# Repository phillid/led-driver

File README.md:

# LM3409HV LED Driver Boards

These are Kicad files for a 450 mA constant current LED driver built around
the LM3409HV, based mostly on the sample schematic in the TI datasheet.

It is designed for 48 volts in and 450 mA CC out, to drive Cree's 16.7 watt
LEDs with Vf of 37 volts.

The PCB measures about 34x32 mm.

More concrete and interesting details to follow as I send the boards to
manufacture, build them up, find the glaring errors I'm too blind to see,
and let the magic smoke out of some components 😜

## Version history

* **v1.1** (BOM change)
	This version changes R2 so that the UVLO is programmed for 43 V turn-on.
	This is to avoid over-driving the LEDs when the power supply voltage is
	low enough to make the driver incapable of reaching the peak LED current,
	which otherwise results in a raising of the average current.
* **v1**
	First, and prototype, revision. Started design in 2017 and finally got
	around to getting boards manufactured in May 2019 after taking a long
	break from the project. These are the first boards to be manufactured.

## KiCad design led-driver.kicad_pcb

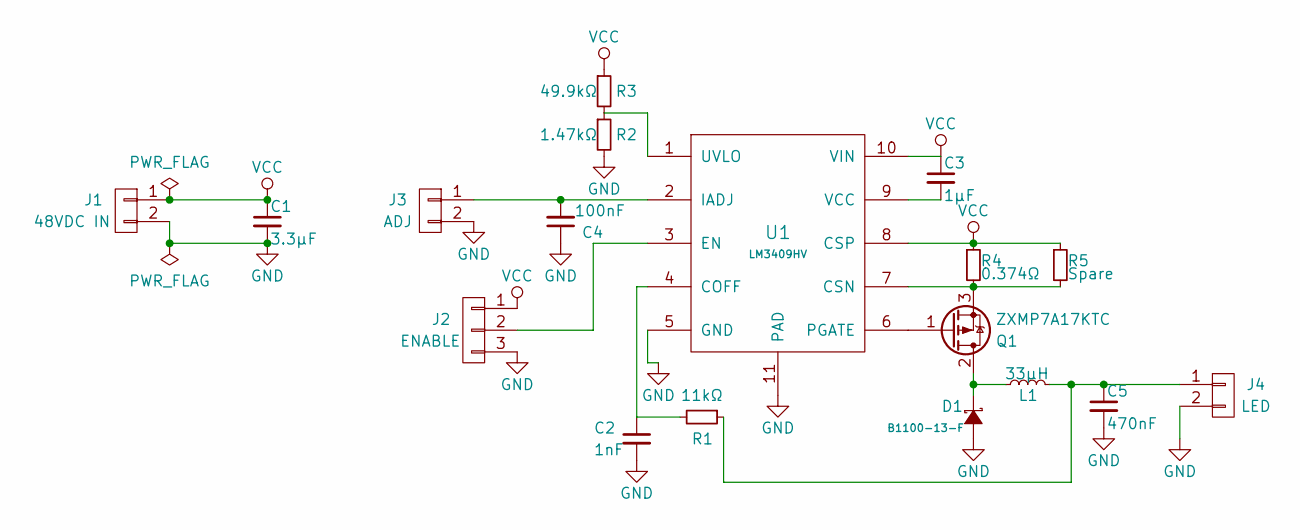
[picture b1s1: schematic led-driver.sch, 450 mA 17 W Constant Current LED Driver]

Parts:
C1: 3.3µF; CP_Elec_5x5.3
C2: 1nF; C_0805
C3: 1µF; C_0805
C4: 100nF; C_0805
C5: 470nF; C_1812
D1: B1100-13-F; D_SMA
J1: 48VDC IN; Pin_Header_Straight_1x02_Pitch2.54mm
J2: ENABLE; Pin_Header_Straight_1x03_Pitch2.54mm
J3: ADJ; Pin_Header_Straight_1x02_Pitch2.54mm
J4: LED; Pin_Header_Straight_1x02_Pitch2.54mm
L1: 33µH; Choke_SMD_7.3x7.3_H3.5
Q1: ZXMP7A17KTC; TO-252-2
R1: 11kΩ; R_0805
R2: 1.47kΩ; R_0805
R3: 49.9kΩ; R_0805
R4: 0.374Ω; R_0805
R5: Spare; R_0805
U1: LM3409HV; MSOP-10-1EP_3x3mm_Pitch0.5mm

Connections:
GND: C1.2, C2.2, C4.1, C5.2, D1.2 (A), J1.2, J2.3, J3.2, J4.2, R2.2, U1.5 (GND), U1.11 (PAD)
unnamed: C2.1, R1.2, U1.4 (COFF)
unnamed: C3.2, U1.9 (VCC)
unnamed: C4.2, J3.1, U1.2 (IADJ)
unnamed: C5.1, J4.1, L1.2, R1.1
unnamed: D1.1 (K), L1.1, Q1.2 (D)
unnamed: J2.2, U1.3 (EN)
unnamed: Q1.1 (G), U1.6 (PGATE)
unnamed: Q1.3 (S), R4.2, R5.2, U1.7 (CSN)
unnamed: R2.1, R3.2, U1.1 (UVLO)
VCC: C1.1, C3.1, J1.1, J2.1, R3.1, R4.1, R5.1, U1.8 (CSP), U1.10 (VIN)

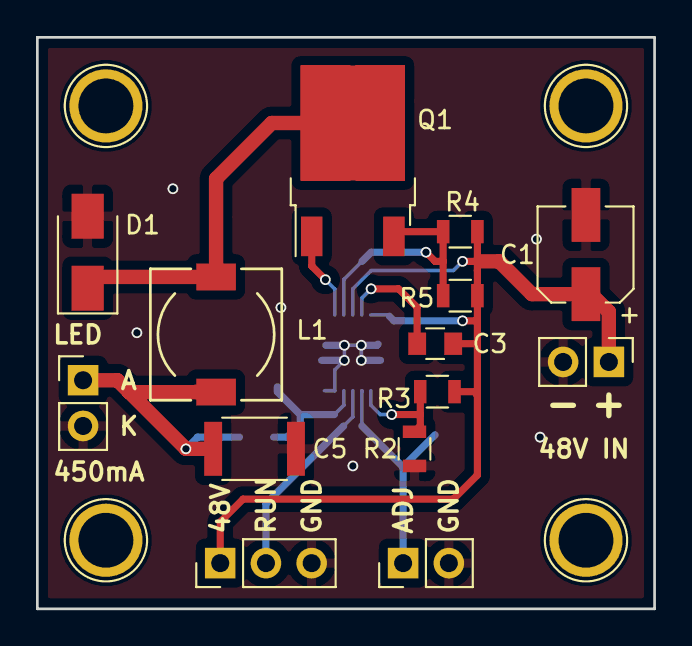
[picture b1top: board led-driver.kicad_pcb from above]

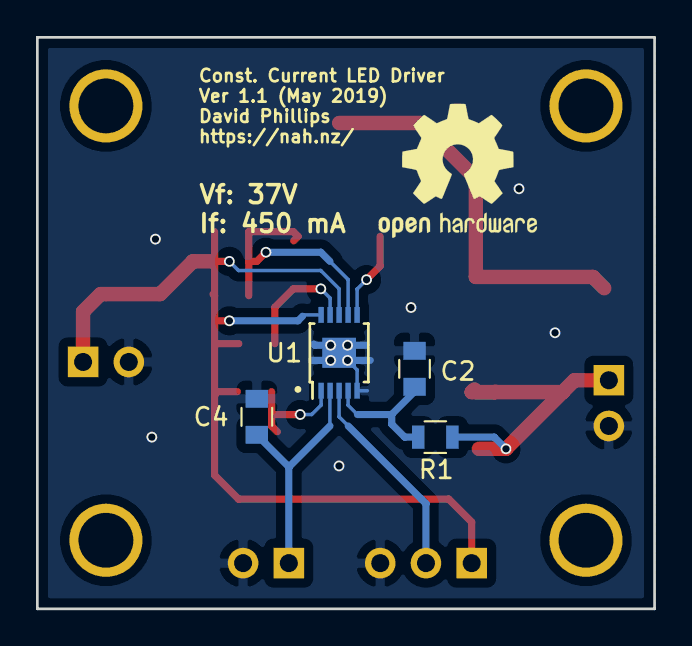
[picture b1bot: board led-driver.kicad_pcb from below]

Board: 2 copper layers, 34.3 x 31.7 mm, 18 parts (4 on the bottom side), 11 nets.

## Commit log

2017-09-06 Add rough working based on datasheet calculations
2017-09-10 Add PCB prototype, schematic, gitignore
2017-09-10 Add README
2017-09-10 Add generated XML to gitignore
2019-05-31 Rescue symbols, minor revisions to PCB
    This commits previous work that took place sporadically between the last
    commit a year and a half ago, and now.
2019-05-31 Reduce clearances, margin on MSOP footprint
    Reduction of the soldermask margin allows soldermask to be placed between the
    landing pads for the leads, which should aid soldering. Reduction of the
    pad clearance should stop DRC from complaining about nets too close together.
2019-05-31 Add PWR_FLAGs to power input
    This quells warnings about connected-but-not-driven nets for GND and VCC
2019-05-31 Add version history to readme
2019-05-31 Readme: Typo, title
2020-01-01 Increase UVLO turn-on to 43 V
    The initial design assumed that the UVLO was a feature of the LM3409 not needed
    by this board. It was set at the datasheet values of 10.1 V turn-on with 1.1 V
    of hysteresis. However, during testing, I have found that the supply will sink
    a maximum of around 600 mA into the load when operated into dropout. The LM3409
    datasheet confirms that this is expected behaviour. Since the supply is
    designed for LEDs modules with a forward voltage of 37 V, this patch changes
2020-01-01 Bump to Version 1.1
2020-01-01 Fix up symbols
